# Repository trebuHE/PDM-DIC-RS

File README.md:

# Master's Thesis Project: Direct Interface Circuits for Resistive Sensors

Master's Thesis project focused on the design and implementation of one-, two-, and three-point calibration methods for MCU direct interface circuits for resistive sensors.

## Aim

The project aims to design and implement a laboratory setup capable of comparing three calibration methods for DIC resistive sensors, taking measurements, and analyzing acquired data. Key milestones include:
- Comprehensive review of measurement methods for resistive sensors
- Designing a laboratory setup including a custom PCB
- Setup assembly
- Writing firmware for test MCUs
- Making a PC app managing data aqusition and storage
- Gathering experimental data regarding three calibration methods
- Analyzing experimental data and drawing conclusions

## Structure

The repository is structured as follows:
- [`/docs`](./docs/) – Research notes, analysis scripts, and useful reference material
- [`/firmware`](./firmware/) – MCU firmware source code
- [`/hardware`](./hardware/) – Hardware design files including custom PCB and 3D printed case
- [`/software`](./software/) - PC data acquisition app source code
- [`/thesis`](./thesis/) – LaTeX source files for the thesis document

## Author

Hubert Mucha (193152)  
Faculty of Electronics, Telecommunications and Informatics  
Gdańsk University of Technology  

## License

This repository and all its contents (hardware design, firmware, and documentation) are licensed under the [**Creative Commons Attribution-NonCommercial-ShareAlike 4.0 International (CC BY-NC-SA 4.0)**](https://creativecommons.org/licenses/by-nc-sa/4.0/legalcode.en) license.

- **Non-Commercial:** You may not use the material for commercial purposes without prior written consent.
- **Attribution:** You must give appropriate credit to the original author.

*Note: The text of the Master's thesis itself is the intellectual property of the author.*

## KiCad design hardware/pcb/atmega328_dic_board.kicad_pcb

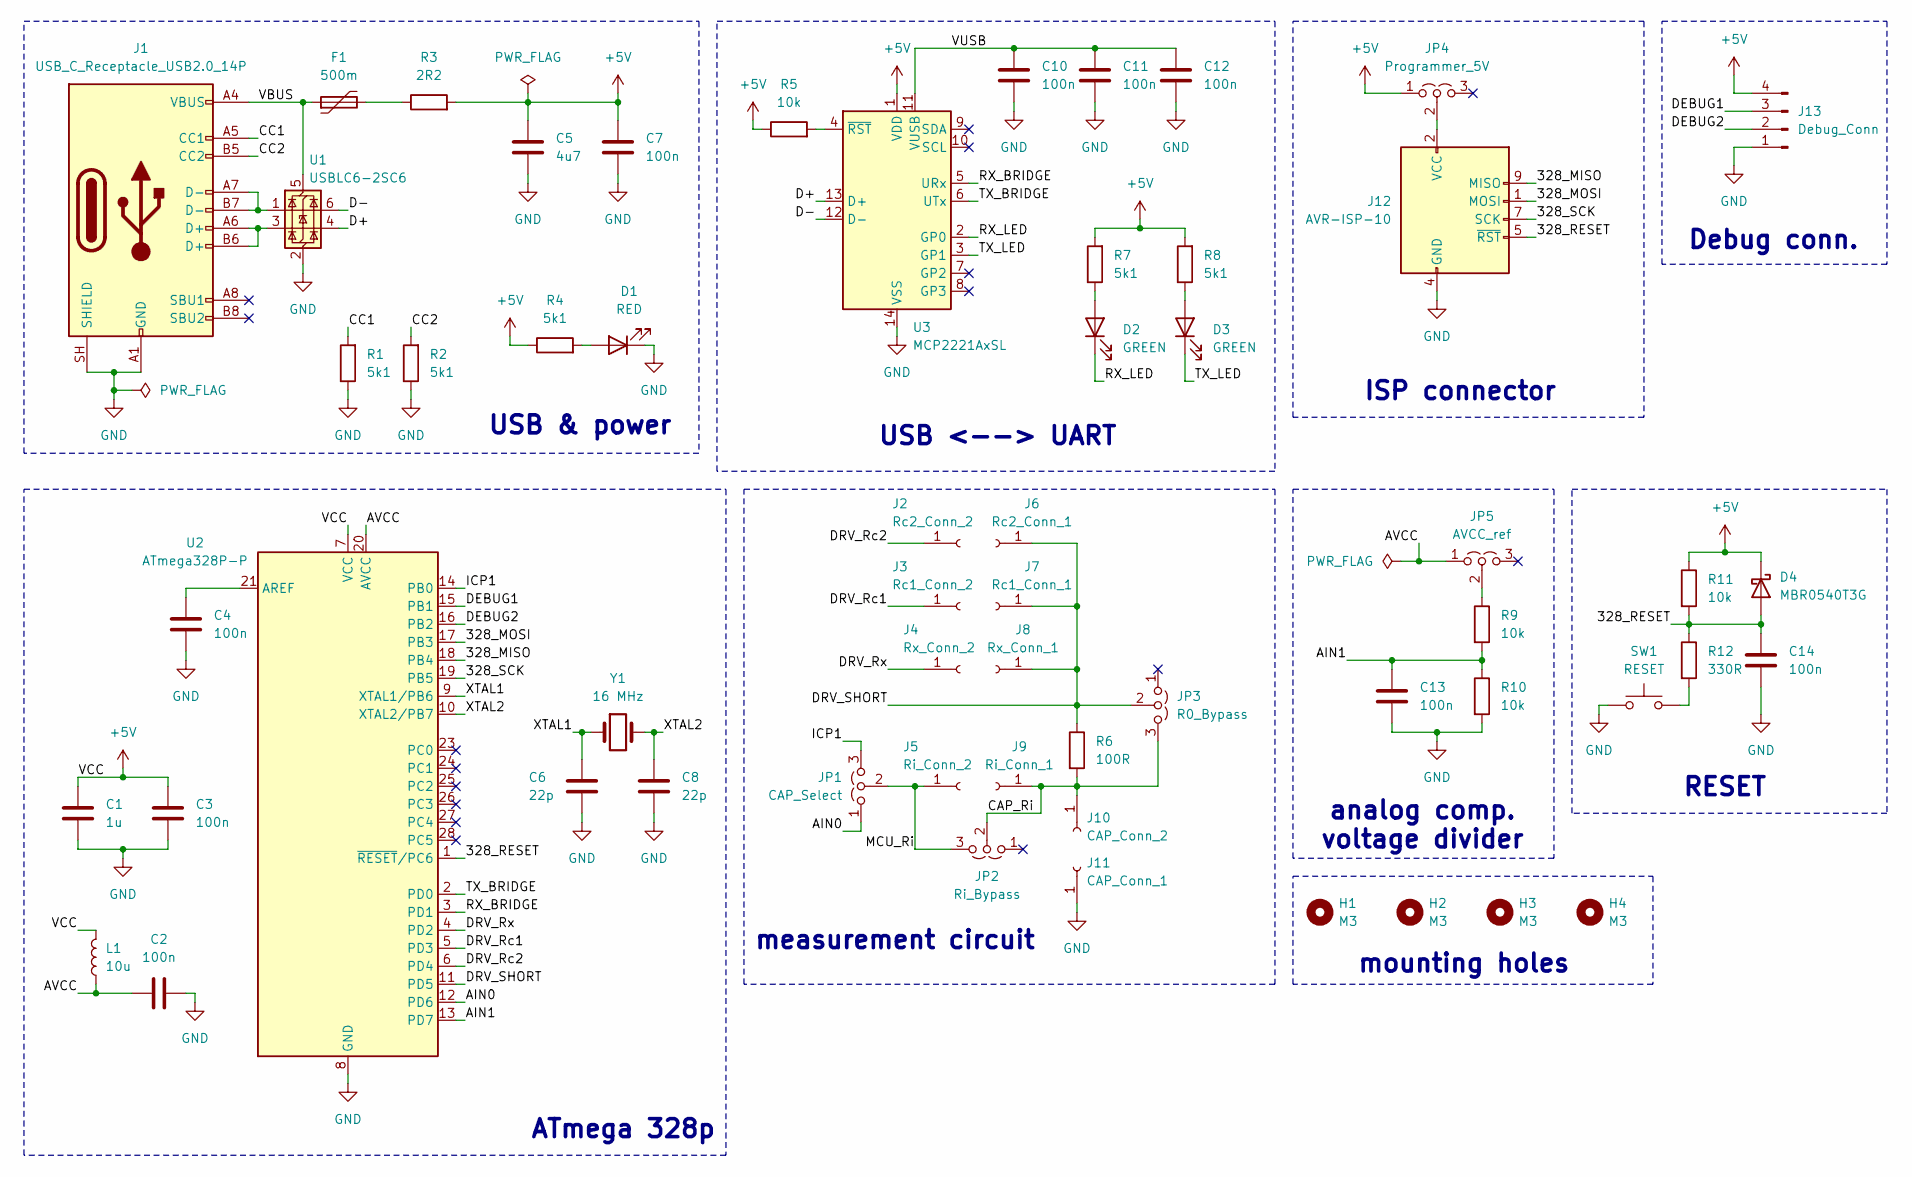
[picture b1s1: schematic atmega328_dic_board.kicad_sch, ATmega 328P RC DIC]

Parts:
C1: 1u; C_0805_2012Metric_Pad1.18x1.45mm_HandSolder
C2, C3, C4, C7, C10, C11, C12, C13, C14: 100n; C_0805_2012Metric_Pad1.18x1.45mm_HandSolder
C5: 4u7; C_0805_2012Metric_Pad1.18x1.45mm_HandSolder
C6, C8: 22p; C_0805_2012Metric_Pad1.18x1.45mm_HandSolder
D1: RED; LED_0805_2012Metric_Pad1.15x1.40mm_HandSolder
D2, D3: GREEN; LED_0805_2012Metric_Pad1.15x1.40mm_HandSolder
D4: MBR0540T3G; D_SOD-123F
F1: 500m; Fuse_1206_3216Metric_Pad1.42x1.75mm_HandSolder
H1, H2, H3, H4: M3; MountingHole_3.2mm_M3
J1: USB_C_Receptacle_USB2.0_14P; USB_C_Receptacle_GCT_USB4105-xx-A_16P_TopMnt_Horizontal
J2: Rc2_Conn_2; PinSocket_1x01_P2.54mm_Vertical
J3: Rc1_Conn_2; PinSocket_1x01_P2.54mm_Vertical
J4: Rx_Conn_2; PinSocket_1x01_P2.54mm_Vertical
J5: Ri_Conn_2; PinSocket_1x01_P2.54mm_Vertical
J6: Rc2_Conn_1; PinSocket_1x01_P2.54mm_Vertical
J7: Rc1_Conn_1; PinSocket_1x01_P2.54mm_Vertical
J8: Rx_Conn_1; PinSocket_1x01_P2.54mm_Vertical
J9: Ri_Conn_1; PinSocket_1x01_P2.54mm_Vertical
J10: CAP_Conn_2; PinSocket_1x01_P2.54mm_Vertical
J11: CAP_Conn_1; PinSocket_1x01_P2.54mm_Vertical
J12: AVR-ISP-10; IDC-Header_2x05_P2.54mm_Vertical
J13: Debug_Conn; PinHeader_1x04_P2.54mm_Vertical
JP1: CAP_Select; PinHeader_1x03_P2.54mm_Vertical
JP2: Ri_Bypass; PinHeader_1x03_P2.54mm_Vertical
JP3: R0_Bypass; PinHeader_1x03_P2.54mm_Vertical
JP4: Programmer_5V; PinHeader_1x03_P2.54mm_Vertical
JP5: AVCC_ref; PinHeader_1x03_P2.54mm_Vertical
L1: 10u; L_0805_2012Metric_Pad1.05x1.20mm_HandSolder
R1, R2, R4, R7, R8: 5k1; R_0805_2012Metric_Pad1.20x1.40mm_HandSolder
R3: 2R2; R_0805_2012Metric_Pad1.20x1.40mm_HandSolder
R5, R9, R10, R11: 10k; R_0805_2012Metric_Pad1.20x1.40mm_HandSolder
R6: 100R; R_0805_2012Metric_Pad1.20x1.40mm_HandSolder
R12: 330R; R_0805_2012Metric_Pad1.20x1.40mm_HandSolder
SW1: RESET; SW_PUSH_6mm
U1: USBLC6-2SC6; SOT-23-6
U2: ATmega328P-P; DIP-28_W7.62mm_Socket
U3: MCP2221AxSL; SOIC-14_3.9x8.7mm_P1.27mm
Y1: 16 MHz; Crystal_SMD_HC49-SD

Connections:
+5V: C1.1, C3.1, C5.1, C7.1, D4.1 (K), J13.4, JP4.1 (A), L1.2, R3.2, R4.1, R5.1, R7.2, R8.2, R11.1, U2.7 (VCC), U3.1 (VDD)
/328_MISO: J12.9 (MISO), U2.18 (PB4)
/328_MOSI: J12.1 (MOSI), U2.17 (PB3)
/328_RESET: C14.1, D4.2 (A), J12.5 (~RST), R11.2, R12.1, U2.1 (~RESET/PC6)
/328_SCK: J12.7 (SCK), U2.19 (PB5)
/AIN0: JP1.1 (A), U2.12 (PD6)
/AIN1: C13.1, R9.2, R10.1, U2.13 (PD7)
/AVCC: C2.1, JP5.1 (A), L1.1, U2.20 (AVCC)
/CAP_Ri: J9.1 (Pin_1_1), J10.1 (Pin_1_1), JP2.2 (C), JP3.3 (B), R6.2
/CC1: J1.A5 (CC1), R1.2
/CC2: J1.B5 (CC2), R2.2
/D+: U1.4 (I/O2), U3.13 (D+)
/D-: U1.6 (I/O1), U3.12 (D-)
/DEBUG1: J13.3, U2.15 (PB1)
/DEBUG2: J13.2, U2.16 (PB2)
/DRV_Rc1: J3.1 (Pin_1_1), U2.5 (PD3)
/DRV_Rc2: J2.1 (Pin_1_1), U2.6 (PD4)
/DRV_Rx: J4.1 (Pin_1_1), U2.4 (PD2)
/DRV_SHORT: J6.1 (Pin_1_1), J7.1 (Pin_1_1), J8.1 (Pin_1_1), JP3.2 (C), R6.1, U2.11 (PD5)
/ICP1: JP1.3 (B), U2.14 (PB0)
/MCU_Ri: J5.1 (Pin_1_1), JP1.2 (C), JP2.3 (B)
/RX_BRIDGE: U2.3 (PD1), U3.5 (URx)
/RX_LED: D2.1 (K), U3.2 (GP0)
/TX_BRIDGE: U2.2 (PD0), U3.6 (UTx)
/TX_LED: D3.1 (K), U3.3 (GP1)
/VBUS: F1.1, J1.A4 (VBUS), J1.A9 (VBUS), J1.B4 (VBUS), J1.B9 (VBUS), U1.5 (VBUS)
/VUSB: C10.1, C11.1, C12.1, U3.11 (VUSB)
/XTAL1: C6.1, U2.9 (XTAL1/PB6), Y1.1
/XTAL2: C8.2, U2.10 (XTAL2/PB7), Y1.2
GND: C1.2, C2.2, C3.2, C4.2, C5.2, C6.2, C7.2, C8.1, C10.2, C11.2, C12.2, C13.2, C14.2, D1.1 (K), J1.A1 (GND), J1.A12 (GND), J1.B1 (GND), J1.B12 (GND), J1.SH (SHIELD), J11.1 (Pin_1_1), J12.4 (GND), J12.6 (GND), J12.8 (GND), J12.10 (GND), J13.1, R1.1, R2.1, R10.2, SW1.1, U1.2 (GND), U2.8 (GND), U2.22 (GND), U3.14 (VSS)
unnamed: D1.2 (A), R4.2
unnamed: D2.2 (A), R7.1
unnamed: D3.2 (A), R8.1
unnamed: F1.2, R3.1
unnamed: J1.A6 (D+), J1.B6 (D+), U1.3 (I/O2)
unnamed: J1.A7 (D-), J1.B7 (D-), U1.1 (I/O1)
unnamed: J12.2 (VCC), JP4.2 (C)
unnamed: JP5.2 (C), R9.1
unnamed: R12.2, SW1.2
unnamed: C4.1, U2.21 (AREF)
unnamed: R5.2, U3.4 (~RST)

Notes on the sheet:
RESET
mounting holes
Debug conn.
analog comp. voltage divider
ISP connector
USB <--> UART
USB & power
measurement circuit
ATmega 328p

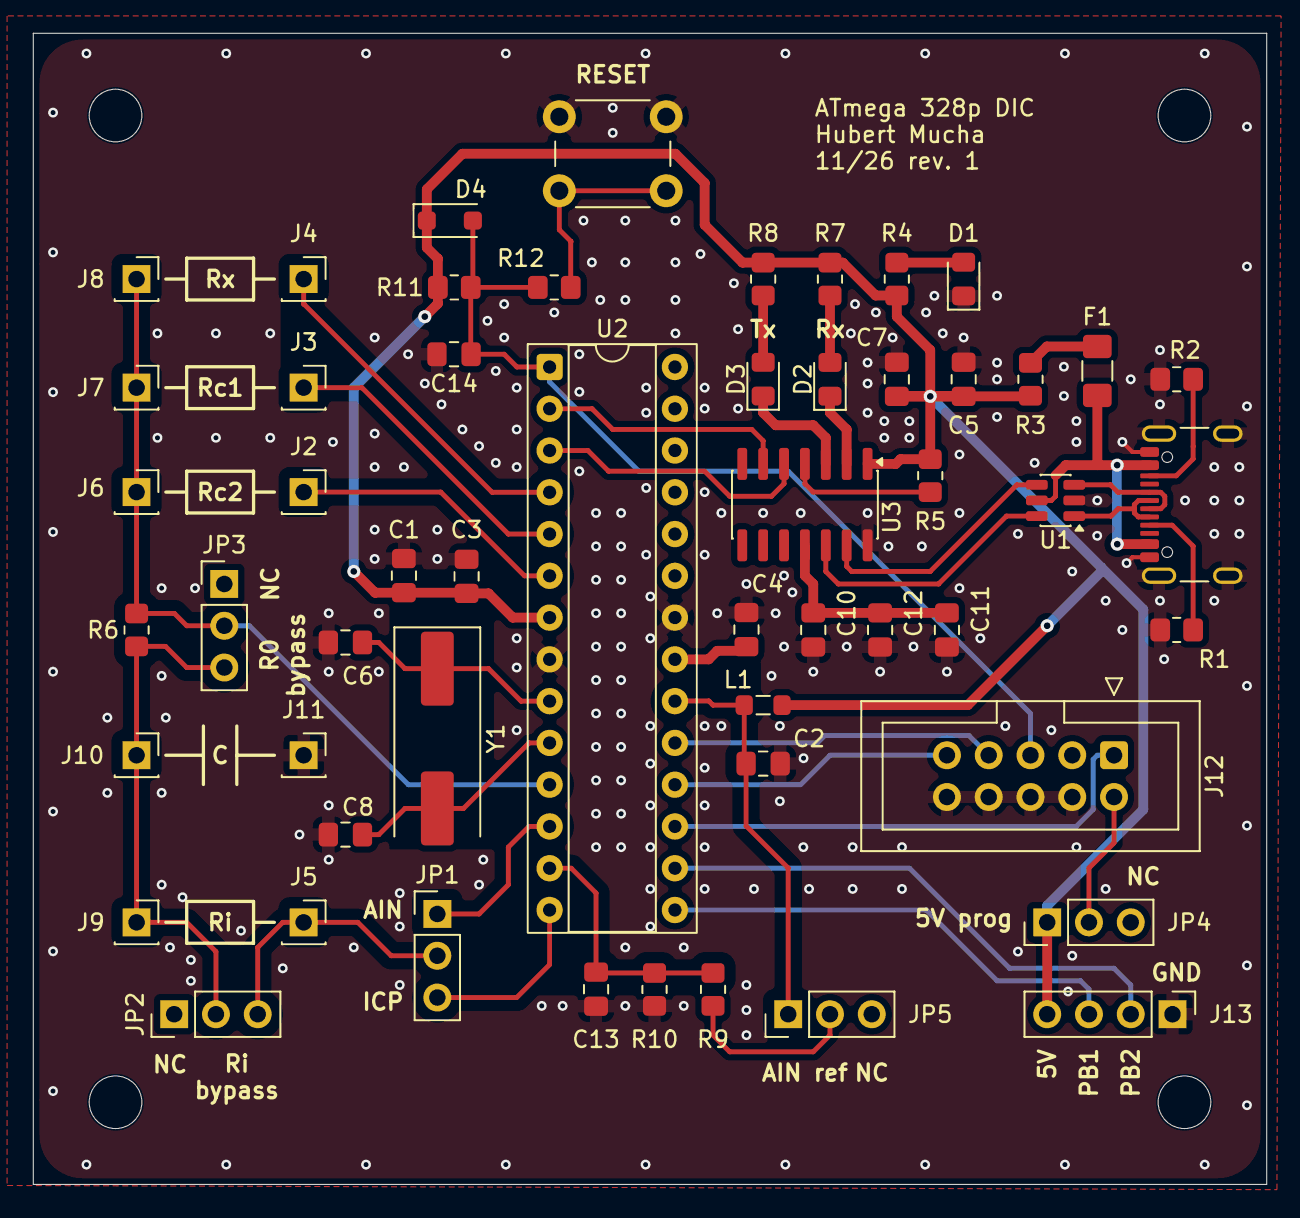
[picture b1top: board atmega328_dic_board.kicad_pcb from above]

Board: 4 copper layers, 75.0 x 70.0 mm, 58 parts (0 on the bottom side), 41 nets.
